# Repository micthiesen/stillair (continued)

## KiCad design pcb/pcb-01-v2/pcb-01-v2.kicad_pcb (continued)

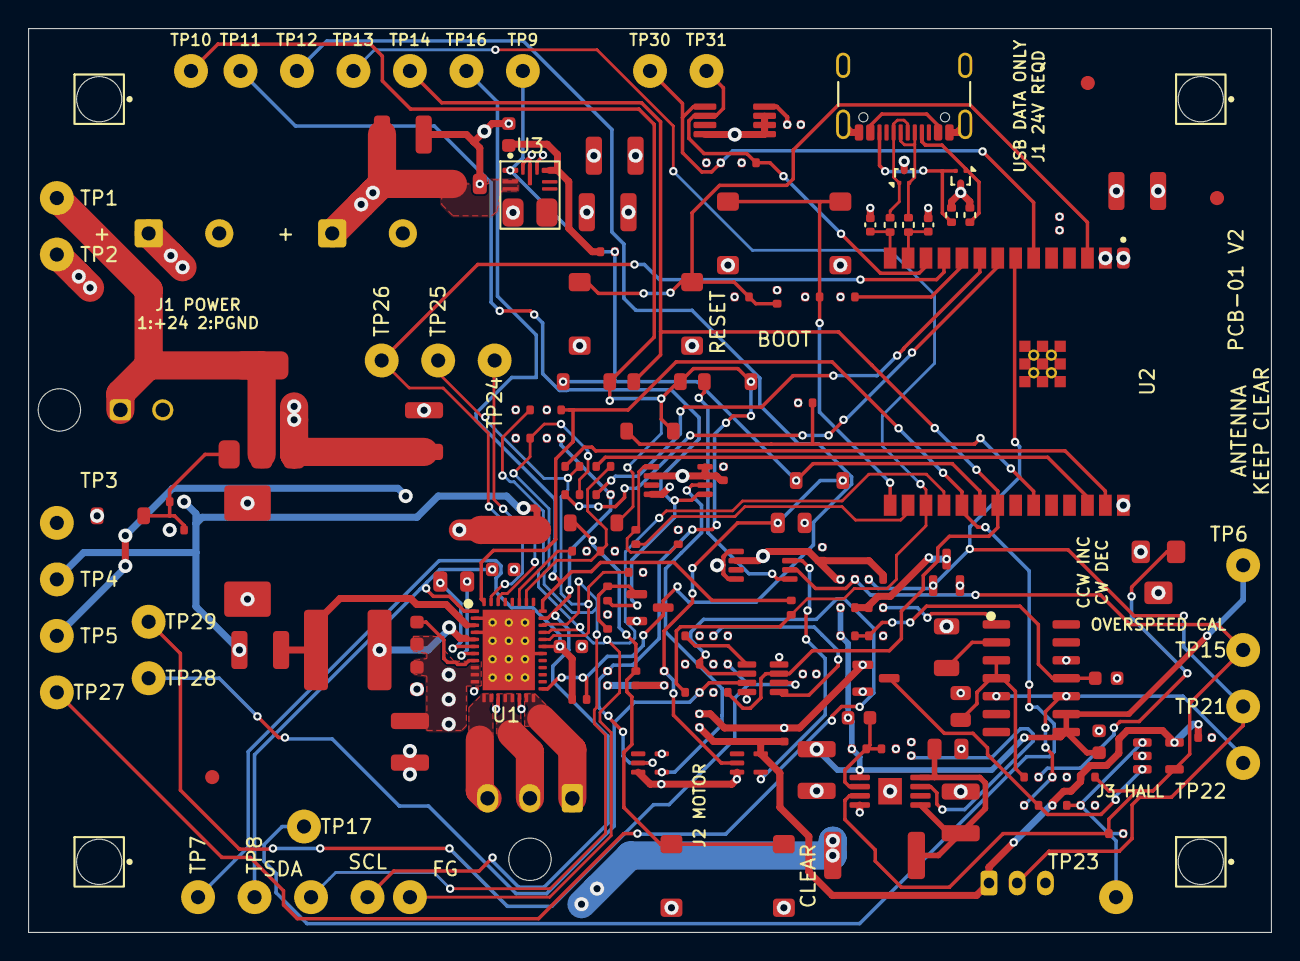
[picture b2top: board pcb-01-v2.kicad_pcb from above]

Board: 4 copper layers, 88.0 x 64.0 mm, 166 parts (0 on the bottom side), 78 nets.

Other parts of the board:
FID1, FID2, FID3: FIDUCIAL; Fiducial_1mm_Mask2mm
H1, H2, H3, H4: M3 NPTH; MountingHole_M3_3.2mm

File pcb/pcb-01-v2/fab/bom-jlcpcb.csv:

Comment,Designator,Footprint,LCSC Part #
10uF 50V X7R 10%,"C3,C4",Capacitor_SMD:C_1210_3225Metric,C2918502
100nF 50V X7R 10%,"C5,C29,C33",Capacitor_SMD:C_0603_1608Metric,C14663
2.2uF 100V X7R 10%,C7,Capacitor_SMD:C_1210_3225Metric,C153036
100nF 100V X7R 10%,"C8,C27",Capacitor_SMD:C_0805_2012Metric,C28233
22uF 25V X7R 10%,"C9,C10,C16,C17",Capacitor_SMD:C_1210_3225Metric,C309062
1uF 50V X5R 10%,"C11,C12,C14,C15",Capacitor_SMD:C_0603_1608Metric,C15849
47nF 100V X7R 10%,C13,Capacitor_SMD:C_0805_2012Metric,C107126
100nF 16V X7R 10%,"C18,C22,C24,C25,C41,C42,C43",Capacitor_SMD:C_0402_1005Metric,C1525
1uF 25V X5R 10%,C19,Capacitor_SMD:C_0402_1005Metric,C52923
100nF 16V X7R 10% U12 bypass,C20,Capacitor_SMD:C_0402_1005Metric,C1525
10uF 25V X5R 10%,C23,Capacitor_SMD:C_0805_2012Metric,C15850
10uF 63V X7R 10%,C26,Capacitor_SMD:C_1210_3225Metric,C437568
10uF 25V X7R 10%,C28,Capacitor_SMD:C_1210_3225Metric,C39232
10nF 50V C0G 5%,C30,Capacitor_SMD:C_0603_1608Metric,C85973
10nF 50V X7R 10%,C31,Capacitor_SMD:C_0402_1005Metric,C15195
100nF 50V C0G 1%,C34,Capacitor_SMD:C_1206_3216Metric,C1864297
2.2uF 50V X5R 10%,C35,Capacitor_SMD:C_0805_2012Metric,C377773
MMSZ5242B-7-F,D1,Diode_SMD:D_SOD-123,C500776
SMCJ24A,D2,Diode_SMD:D_SMC,C135154
BAT54W-G3-08,"D3,D4,D5,D6,D7,D8",Diode_SMD:D_SOD-123,C3313038
BAT54SLT1G,D9,Package_TO_SOT_SMD:SOT-23,C19726
USB4105-GF-A,J4,Connector_USB:USB_C_Receptacle_GCT_USB4105-xx-A_16P_TopMnt_Horizontal,C3020560
SWPA6045S470MT,L1,Inductor_SMD:L_Sunlord_SWPA6045S,C36414
DMP6023LE-13,Q1,Package_TO_SOT_SMD:SOT-223-3_TabPin2,C154901
2N7002K-7,"Q2,Q3",Package_TO_SOT_SMD:SOT-23,C85047
10k,R1,Resistor_SMD:R_0402_1005Metric,C25744
100k,R2,Resistor_SMD:R_0402_1005Metric,C25741
10k 1%,"R3,R8,R9,R11,R12,R13,R18,R29,R30,R32,R33,R34,R35,R37,R42,R43,R44,R46,R47,R49,R50",Resistor_SMD:R_0402_1005Metric,C25744
4.7k 1%,"R4,R5,R6,R7,R19,R20,R28",Resistor_SMD:R_0402_1005Metric,C105871
100k 1%,"R10,R25,R27,R31",Resistor_SMD:R_0402_1005Metric,C25741
100ohm 1%,"R14,R15,R24,R36,R38,R45",Resistor_SMD:R_0402_1005Metric,C25076
0ohm I2C isolation link,"R16,R17",Resistor_SMD:R_0402_1005Metric,C17168
1k 1%,R26,Resistor_SMD:R_0402_1005Metric,C11702
47ohm 1W 1%,R39,Resistor_SMD:R_2512_6332Metric,C3000771
910k 0.1%,R40,Resistor_SMD:R_0402_1005Metric,C3921007
100k 0.1%,R41,Resistor_SMD:R_0402_1005Metric,C852472
562k 1%,R48,Resistor_SMD:R_0402_1005Metric,C4323390
47.0k 0.1%,R51,Resistor_SMD:R_0402_1005Metric,C728561
10.0k 0.1%,R52,Resistor_SMD:R_0402_1005Metric,C190095
35.7k 1%,R53,Resistor_SMD:R_0402_1005Metric,C2998133
90.9k 0.1%,R54,Resistor_SMD:R_0402_1005Metric,C2079068
22R,"R58,R59",Resistor_SMD:R_0402_1005Metric,C25092
5.1k,"R60,R61",Resistor_SMD:R_0402_1005Metric,C25905
3224W-1-204E,RV1,Potentiometer_SMD:Potentiometer_Bourns_3224W_Vertical,C55072
PTS645SK43SMTR92LFS,"SW1,SW2,SW3",Button_Switch_SMD:SW_SPST_PTS645Sx43SMTR92,C221871
MCF8316DVRGFR,U1,pcb01-parts:MCF8316D_RGF0040E,C47122159
ESP32-C6-WROOM-1-N8,U2,pcb01-v2-parts:ESP32-C6-WROOM-1,C5366877
TPSM365R6V3RDNR,U3,pcb01-parts:TPSM365R6_RDN0011A,C18208843
TPS7A1601ADGNR,U4,Package_SO:MSOP-8-1EP_3x3mm_P0.65mm_EP1.68x1.88mm,C6886485
SN74LVC1G74DCTR,"U5,U6",pcb01-parts:TI_SM8_DCT0008A,C840104
TPS3435CAKAGDDFR,U7,pcb01-v2-parts:SOT-23-8_P0.65mm_Clearance0.20,C6339182
TLV1701AIDBVR,U9,Package_TO_SOT_SMD:SOT-23-5,C130035
SN74LVC1G17DCKR,"U10,U11",Package_TO_SOT_SMD:SOT-353_SC-70-5,C10425
TMP1075DGKR,U12,pcb01-v2-parts:VSSOP-8_3x3mm_P0.65mm_Clearance0.20,C2864807
TPD2EUSB30DRTR,"U13,U14",Package_TO_SOT_SMD:Texas_DRT-3,C97502

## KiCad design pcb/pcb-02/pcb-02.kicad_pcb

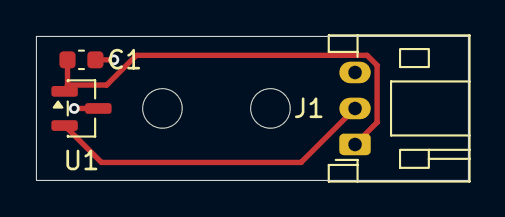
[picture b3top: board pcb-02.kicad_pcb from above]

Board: 2 copper layers, 24.0 x 8.0 mm, 5 parts (0 on the bottom side), 3 nets.

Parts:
C1: 100nF; C_0603_1608Metric
H1, H2: MountingHole; MountingHole_2.2mm_M2
J1: HALL_TO_J3; JST_PH_S3B-PH-K_1x03_P2.00mm_Horizontal
U1: DRV5033FAQDBZR; SOT-23

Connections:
/3V3: C1.1, J1.1, U1.1 (VCC)
/AGND: C1.2, J1.3, U1.3 (GND)
/HALL_TACH: J1.2, U1.2 (OUT)

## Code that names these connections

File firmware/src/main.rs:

//! Stillair ceiling-fan supervisor firmware (stub).
//!
//! Runs on the ESP32-C6-MINI-1-H4 on the custom 78 × 58 mm controller board.
//! The supervisor configures the MCF8316D over I²C and commands speed/direction;
//! it never switches motor phases. The full behavioral contract lives in
//! `docs/controls.md`; the board pinout lives in `docs/electrical.md` (SCH-04).
//!
//! GPIO map (verified against the ESP32-C6-MINI-1 datasheet; GPIO15 is the only strap
//! pin used — its JTAG-select strap is ignored with default eFuses and the external
//! pull-up satisfies its no-float requirement):
//!
//! | GPIO    | Signal                       |
//! |---------|------------------------------|
//! | 0 / 1   | SDA / SCL (MCF I²C)          |
//! | 2       | SPEED PWM                    |
//! | 3       | DIR                          |
//! | 6       | NTC ADC (optional, ADC1_CH6) |
//! | 7       | HALL_TACH sense (plausibility check input) |
//! | 12 / 13 | USB D− / D+                  |
//! | 14      | MCF ALARM (active-high)      |
//! | 15      | MCU_CLEAR_N (open-drain out) |
//! | 16 / 17 | UART TX / RX                 |
//! | 18      | permission ARM_PULSE         |
//! | 19      | watchdog heartbeat           |
//! | 20      | MCF FG                       |
//! | 21      | MCF nFAULT                   |
//! | 22      | 3.3 V PGOOD                  |
//! | 23      | watchdog WDO diagnostic      |

#![no_std]
#![no_main]
// Stub scaffolding: modules define the eventual API surface before anything
// consumes it. Remove once the hardware interfaces are wired up.
#![allow(dead_code)]

use embassy_time::{Duration, Timer};
use esp_backtrace as _;
use esp_hal::timer::timg::TimerGroup;

mod config;
mod mcf8316;
mod state;

esp_bootloader_esp_idf::esp_app_desc!();

#[esp_rtos::main]
async fn main(spawner: embassy_executor::Spawner) {
    esp_println::logger::init_logger_from_env();

    let peripherals = esp_hal::init(esp_hal::Config::default());

    // Heap is only needed once the radio (Wi-Fi / Matter) comes online.
    esp_alloc::heap_allocator!(size: 72 * 1024);

    let timg0 = TimerGroup::new(peripherals.TIMG0);
    let sw_int =
        esp_hal::interrupt::software::SoftwareInterruptControl::new(peripherals.SW_INTERRUPT);
    esp_rtos::start(timg0.timer0, sw_int.software_interrupt0);

    log::info!("stillair supervisor boot (stub)");

    // TODO: bring up the hardware interfaces once the V1 board exists:
    //   - I²C to the MCF8316D (GPIO0/1) and initial register verification
    //   - watchdog heartbeat output on GPIO19 (2 Hz, serviced on the falling edge)
    //   - SPEED PWM (GPIO2), DIR (GPIO3), ARM_PULSE (GPIO18), MCU_CLEAR_N
    //   - FG (GPIO20), nFAULT (GPIO21), PGOOD (GPIO22), WDO (GPIO23) inputs
    //   - Wi-Fi + Matter via rs-matter-embassy (git dep; see docs/controls.md > Home
    //     integration for the pin/patch strategy). esp-radio / embassy-net are already in
    //     the dep tree.

    spawner.spawn(supervisor_task().unwrap());
    spawner.spawn(heartbeat_task().unwrap());
}

/// Drives the fan state machine. Stub: ticks the (empty) supervisor.
#[embassy_executor::task]
async fn supervisor_task() {
    let mut supervisor = state::Supervisor::new();
    loop {
        supervisor.tick();
        Timer::after(Duration::from_millis(100)).await;
    }
}

/// Will service the TPS3435 watchdog (2 Hz square wave on GPIO19). The watchdog
/// starts monitoring immediately at power-up; until firmware arms the permission
/// latch that is safe because U5 powers up cleared. Stub: logs instead of toggling.
#[embassy_executor::task]
async fn heartbeat_task() {
    let half_period = Duration::from_hz(u64::from(config::WATCHDOG_HEARTBEAT_HZ) * 2);
    let mut ticks: u32 = 0;
    loop {
        // TODO: toggle the GPIO19 heartbeat output here.
        ticks = ticks.wrapping_add(1);
        if ticks.is_multiple_of(config::WATCHDOG_HEARTBEAT_HZ * 2 * 30) {
            log::info!("heartbeat alive ({ticks} half-periods)");
        }
        Timer::after(half_period).await;
    }
}

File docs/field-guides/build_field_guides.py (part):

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
    x, y, w, h = s.panel("BARE DEV-BOARD INPUT SIMULATION", 160, AMBER_BG, AMBER, AMBER)
    s.checkboxes([
        "GPIO22 to 3V3: PGOOD good.",
        "GPIO21 to 3V3: nFAULT idle high.",
        "GPIO14 to GND: ALARM idle low.",
        "Without real FG edges, Starting must fault NoRotation after 15 s. This is expected.",
    ], x + 14, y + 112, w - 28, 9.2)

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    x, y, w, h = s.panel("SET UP THE TEST YOU WILL ACTUALLY RUN", 260, BLUE_BG, BLUE, BLUE)
    s.checkboxes([
        "Secure the rotor and external drive so the setup cannot walk or tip; clear the rotor plane and nearby loose objects.",
        "Disconnect GL100 phases from PCB-01. PCB-02 may stay powered for Hall speed; the analog lock may latch without stopping the external drive.",
        "Use PCB-02 Hall telemetry or the external drive's own credible speed readout; record which source was used.",
        "Keep the ordinary power switch, low-voltage cutoff, or plug reachable from outside the sweep.",
        "Start at the lowest useful speed and advance only while motion and sound remain normal.",
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    c.setFillColor(RED); c.setFont("Helvetica-Bold", 7.5)
    c.drawString(47, 268, "SOLDER ORDER: U8 -> C34 -> J1/J2 -> C1/C2 -> INSPECT -> F1 LAST")

    mini_card(c, "1 + 2  C1 / C2", "EEU-FR1H471, 470 uF 50 V. Positive lead to board +; negative stripe to pin 2 / PGND. Seat square without crushing bung.", 35, 190, 258, 76, GREEN, GREEN_BG)
    mini_card(c, "3  F1 - INSTALL LAST", "Low-profile tinned copper link across the 1206 pads. Near-zero ohms after soldering. External wall-side 3 A fuse remains mandatory.", 305, 190, 272, 76, RED, RED_BG)
    mini_card(c, "4 + 5  CONNECTORS", "J1 43045-0200; J2 43650-0300. Larger chisel tip. Tack one electrical pin, square and fully seat housing, then finish. Locating pegs are not soldered.", 35, 104, 258, 76, BLUE, BLUE_BG)
    mini_card(c, "6  U8  /  7  C34", "U8 LM2907M/NOPB: notch/dimple to pin-1 marker, tack pin 1 then diagonal pin 8, flux and drag-solder. C34 C1206C104K3GACTU: 100 nF C0G 25 V +/-10%, spanning the smaller 0603 site, not shorting it.", 305, 104, 272, 76, PURPLE, PURPLE_BG)
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    arrow(c, 488, 484, 560, 484, GREEN, 2)
    c.setFillColor(GREEN); c.setFont("Helvetica-Bold", 7.5); c.drawRightString(480, 482, "J1 / CABLE EXITS RIGHT")

    mini_card(c, "1  C1", "C0603C104K5RACTU, 100 nF 50 V X7R, 0603. Pin 1 / 3V3 is left; pin 2 / AGND is right.", 35, 399, 170, 70, GREEN, GREEN_BG)
    mini_card(c, "2  U1", "DRV5033FAQDBZR, SOT-23. Match package index to board triangle. Pin 1 upper-left = 3V3; pin 2 lower-left = HALL_TACH; pin 3 right = AGND.", 216, 399, 181, 70, PURPLE, PURPLE_BG)
    mini_card(c, "3  J1", "S3B-PH-K-S side-entry JST-PH. Top to bottom in this view: 3 AGND, 2 HALL_TACH, 1 3V3. Iron-solder last.", 408, 399, 169, 70, BLUE, BLUE_BG)

    c.setFillColor(INK); c.setFont("Helvetica-Bold", 11); c.drawString(35, 377, "IRON METHOD: THIN SOLDER WIRE + FLUX")
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    x, y, w, h = s.panel("WHAT COUNTS AS DONE", 145, GREEN_BG, GREEN, GREEN)
    s.checkbox_grid([
        ("A result is measured and recorded, not just observed.", "A failed gate stops the next powered stage."),
        ("Connector polarity and pin order are proved end-to-end.", "After loaded MPET, verify config before start/speed qualification."),
        ("Installed unpowered checks precede gradual loaded work.", "Normal safety firmware + long USB J6; cutoff outside sweep."),
    ], x + 14, y + 100, w / 2 - 2, 8.4)
    x, y, w, h = s.panel("BOUNDARIES KEPT OUT OF THIS ACTIVE BINDER", 120, GRAY_BG)
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            line_y -= 11
        box_top = box_y - 11
    c.setFillColor(INK); c.setFont("Helvetica-Bold",10); c.drawString(35, 507, "BARE DEV-BOARD INPUT JUMPERS")
    mini_card(c,"GPIO22 -> 3V3","PGOOD good",35,424,160,65,GREEN,GREEN_BG)
    mini_card(c,"GPIO21 -> 3V3","nFAULT idle high",226,424,160,65,GREEN,GREEN_BG)
    mini_card(c,"GPIO14 -> GND","ALARM idle low",417,424,160,65,BLUE,BLUE_BG)
    step_strip(c,["config stage","Starting","15 s, no FG","NoRotation fault"],35,366,542,RED)
    c.setFillColor(RED); c.setFont("Helvetica-Bold",8); c.drawCentredString(306,350,"EXPECTED ON A BARE BOARD; IT DOES NOT GENERATE FG EDGES")
    s.y = 340
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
